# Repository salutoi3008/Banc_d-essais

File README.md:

#  Dépôt pour Mini-Projet de banc d'essais BTS CIEL2
   
  Ce dépôt contient les documents du mini-projet consacré à un banc d'essais pour des écran LCD

Il contient plusieurs dossiers:

   - Un dossier contenant le programme de test réalisé en C
   - Un dossier contenant le schéma du projet ainsi que le PCB lui étant associé
   - Un autre dossier avec tous les documents utilisés pour le projet

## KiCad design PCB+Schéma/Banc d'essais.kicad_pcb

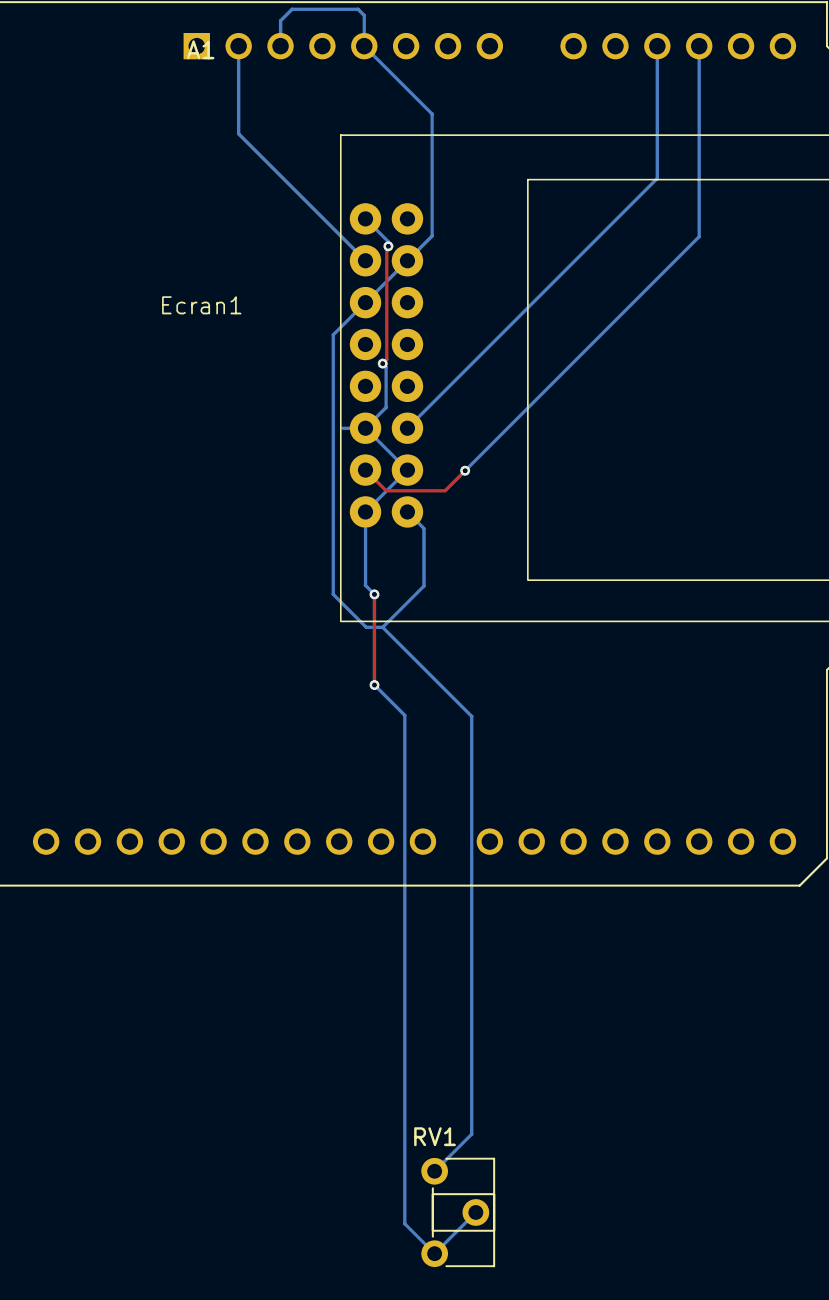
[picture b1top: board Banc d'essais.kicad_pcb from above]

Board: 2 copper layers, 3 parts (0 on the bottom side), 5 nets.

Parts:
A1: Arduino_UNO_R3
Ecran1: Sans titre
RV1: R_Potentiometer; Potentiometer_ACP_CA6-H2,5_Horizontal

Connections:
Earth: Ecran1.2 (VSS), Ecran1.3 (V0), Ecran1.5 (R/W), Ecran1.16 (K), RV1.2, RV1.3
unnamed: A1.3 (~RESET), A1.4 (3V3), A1.5 (+5V), Ecran1.1 (VDD), Ecran1.12 (DB5), Ecran1.13 (DB6), RV1.1
unnamed: A1.11 (A2), Ecran1.6 (E)
unnamed: A1.12 (A3), Ecran1.4 (RS)
unnamed: A1.2 (IOREF), Ecran1.14 (DB7)
